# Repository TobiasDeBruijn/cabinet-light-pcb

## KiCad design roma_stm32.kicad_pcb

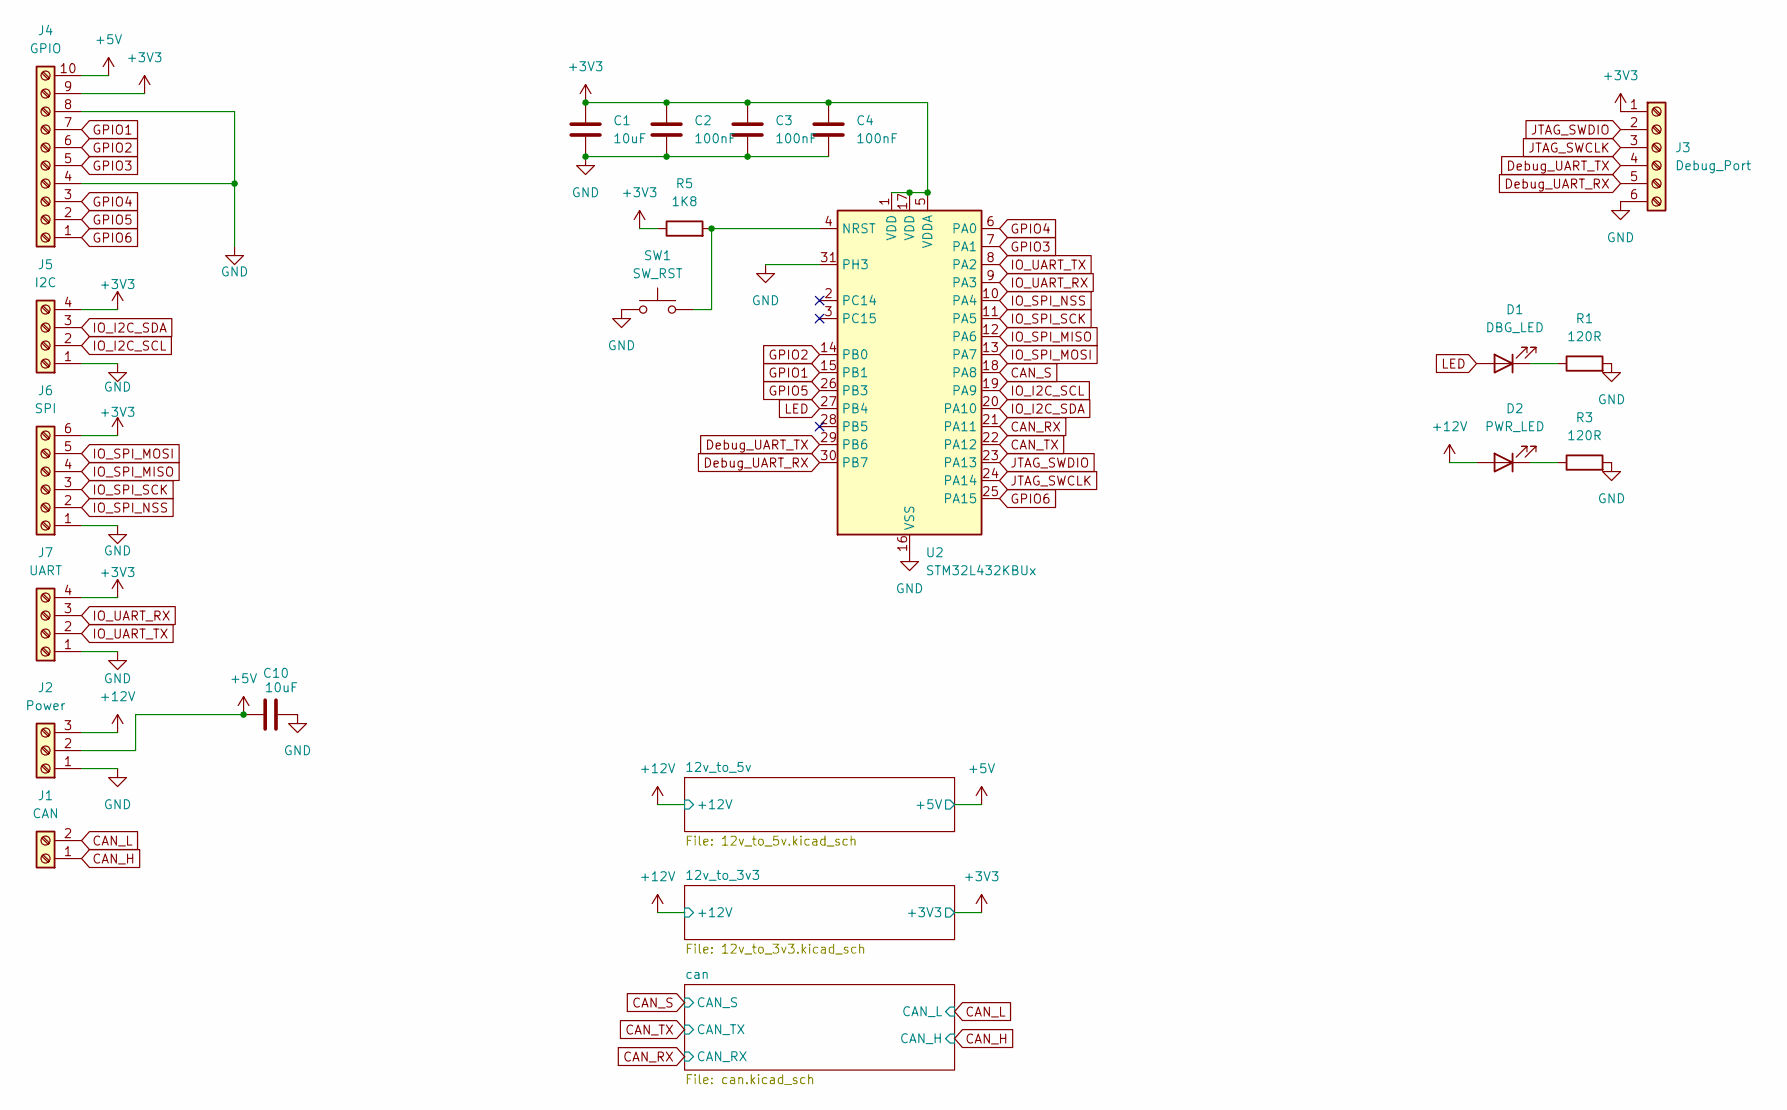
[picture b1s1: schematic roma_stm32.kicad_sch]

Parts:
C1, C10: 10uF; C_0805_2012Metric
C2, C3, C4: 100nF; C_0603_1608Metric
D1: DBG_LED; LED_0805_2012Metric
D2: PWR_LED; LED_0805_2012Metric
J1: CAN; TerminalBlock_Phoenix_PT-1,5-2-5.0-H_1x02_P5.00mm_Horizontal
J2: Power; TerminalBlock_Phoenix_PT-1,5-3-5.0-H_1x03_P5.00mm_Horizontal
J3: Debug_Port; TerminalBlock_Phoenix_PT-1,5-6-5.0-H_1x06_P5.00mm_Horizontal
J4: GPIO; TerminalBlock_Phoenix_PT-1,5-10-5.0-H_1x10_P5.00mm_Horizont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
J5: I2C; TerminalBlock_Phoenix_PT-1,5-4-5.0-H_1x04_P5.00mm_Horizontal
J6: SPI; TerminalBlock_Phoenix_PT-1,5-6-5.0-H_1x06_P5.00mm_Horizontal
J7: UART; TerminalBlock_Phoenix_PT-1,5-4-5.0-H_1x04_P5.00mm_Horizontal
R1, R3: 120R; R_0805_2012Metric
R5: 1K8; R_0603_1608Metric
SW1: SW_RST; SW_Push_1P1T_XKB_TS-1187A
U2: STM32L432KBUx; QFN-32-1EP_5x5mm_P0.5mm_EP3.45x3.45mm

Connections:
+3V3: C1.1, C2.1, C3.1, C4.1, J3.1, J4.9, J5.4, J6.6, J7.4, R5.1, U2.1 (VDD), U2.5 (VDDA), U2.17 (VDD); also elsewhere on the board
+5V: C10.1, J2.2, J4.10; also elsewhere on the board
+12V: D2.2 (A), J2.3; also elsewhere on the board
CAN_H: J1.1; also elsewhere on the board
CAN_L: J1.2; also elsewhere on the board
CAN_RX: U2.21 (PA11); also elsewhere on the board
CAN_S: U2.18 (PA8); also elsewhere on the board
CAN_TX: U2.22 (PA12); also elsewhere on the board
Debug_UART_RX: J3.5, U2.30 (PB7)
Debug_UART_TX: J3.4, U2.29 (PB6)
GND: C1.2, C2.2, C3.2, C4.2, C10.2, J2.1, J3.6, J4.4, J4.8, J5.1, J6.1, J7.1, R1.2, R3.2, SW1.1, U2.16 (VSS), U2.31 (PH3), U2.32 (VSS), U2.33 (VSS); also elsewhere on the board
GPIO1: J4.7, U2.15 (PB1)
GPIO2: J4.6, U2.14 (PB0)
GPIO3: J4.5, U2.7 (PA1)
GPIO4: J4.3, U2.6 (PA0)
GPIO5: J4.2, U2.26 (PB3)
GPIO6: J4.1, U2.25 (PA15)
IO_I2C_SCL: J5.2, U2.19 (PA9)
IO_I2C_SDA: J5.3, U2.20 (PA10)
IO_SPI_MISO: J6.4, U2.12 (PA6)
IO_SPI_MOSI: J6.5, U2.13 (PA7)
IO_SPI_NSS: J6.2, U2.10 (PA4)
IO_SPI_SCK: J6.3, U2.11 (PA5)
IO_UART_RX: J7.3, U2.9 (PA3)
IO_UART_TX: J7.2, U2.8 (PA2)
JTAG_SWCLK: J3.3, U2.24 (PA14)
JTAG_SWDIO: J3.2, U2.23 (PA13)
LED: D1.2 (A), U2.27 (PB4)
unnamed: D1.1 (K), R1.1
unnamed: D2.1 (K), R3.1
unnamed: R5.2, SW1.2, U2.4 (NRST)

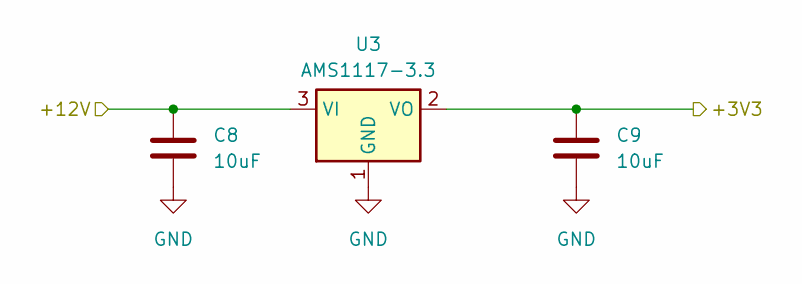
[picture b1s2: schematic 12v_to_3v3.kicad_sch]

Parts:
C8, C9: 10uF; C_0805_2012Metric
U3: AMS1117-3.3; SOT-223-3_TabPin2

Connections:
+3V3: C9.1, U3.2 (VO); also elsewhere on the board
+12V: C8.1, U3.3 (VI); also elsewhere on the board
GND: C8.2, C9.2, U3.1 (GND); also elsewhere on the board

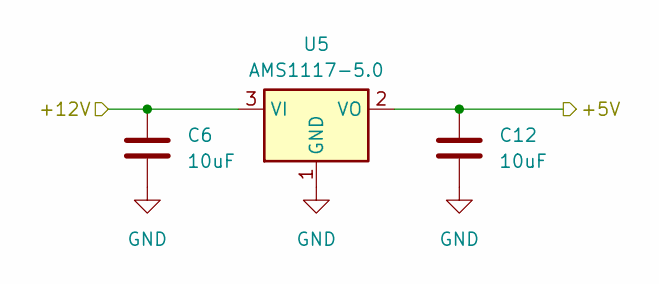
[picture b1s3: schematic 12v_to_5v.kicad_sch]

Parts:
C6, C12: 10uF; C_0805_2012Metric
U5: AMS1117-5.0; SOT-223-3_TabPin2

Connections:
+5V: C12.2, U5.2 (VO); also elsewhere on the board
+12V: C6.2, U5.3 (VI); also elsewhere on the board
GND: C6.1, C12.1, U5.1 (GND); also elsewhere on the board

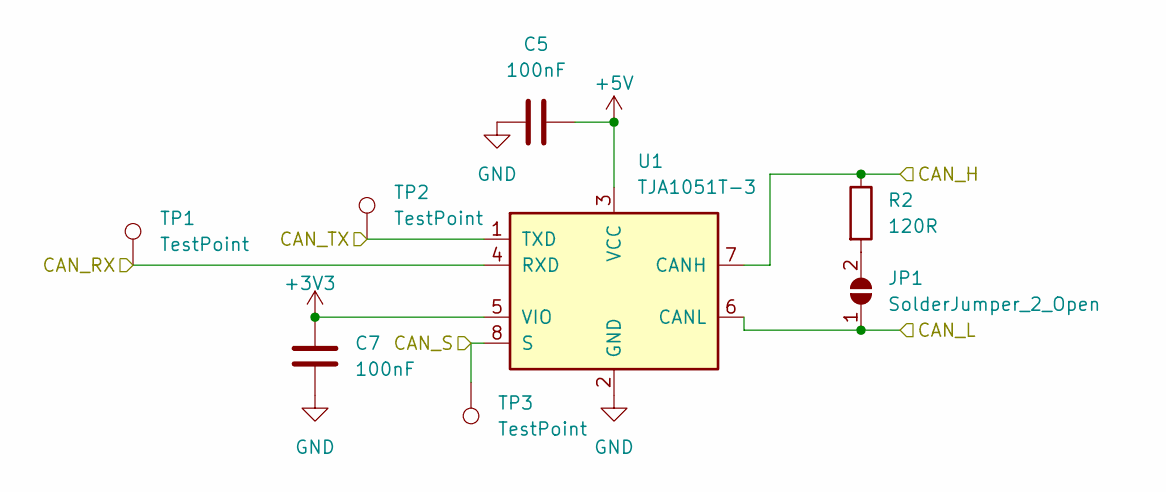
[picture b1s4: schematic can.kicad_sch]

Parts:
C5, C7: 100nF; C_0603_1608Metric
JP1: SolderJumper_2_Open; SolderJumper-2_P1.3mm_Open_Pad1.0x1.5mm
R2: 120R; R_0603_1608Metric
TP1, TP2, TP3: TestPoint; TestPoint_Pad_D1.0mm
U1: TJA1051T-3; SOIC-8_3.9x4.9mm_P1.27mm

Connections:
+3V3: C7.2, U1.5 (VIO); also elsewhere on the board
+5V: C5.2, U1.3 (VCC); also elsewhere on the board
CAN_H: R2.1, U1.7 (CANH); also elsewhere on the board
CAN_L: JP1.1 (A), U1.6 (CANL); also elsewhere on the board
CAN_RX: TP1.1, U1.4 (RXD); also elsewhere on the board
CAN_S: TP3.1, U1.8 (S); also elsewhere on the board
CAN_TX: TP2.1, U1.1 (TXD); also elsewhere on the board
GND: C5.1, C7.1, U1.2 (GND); also elsewhere on the board
unnamed: JP1.2 (B), R2.2

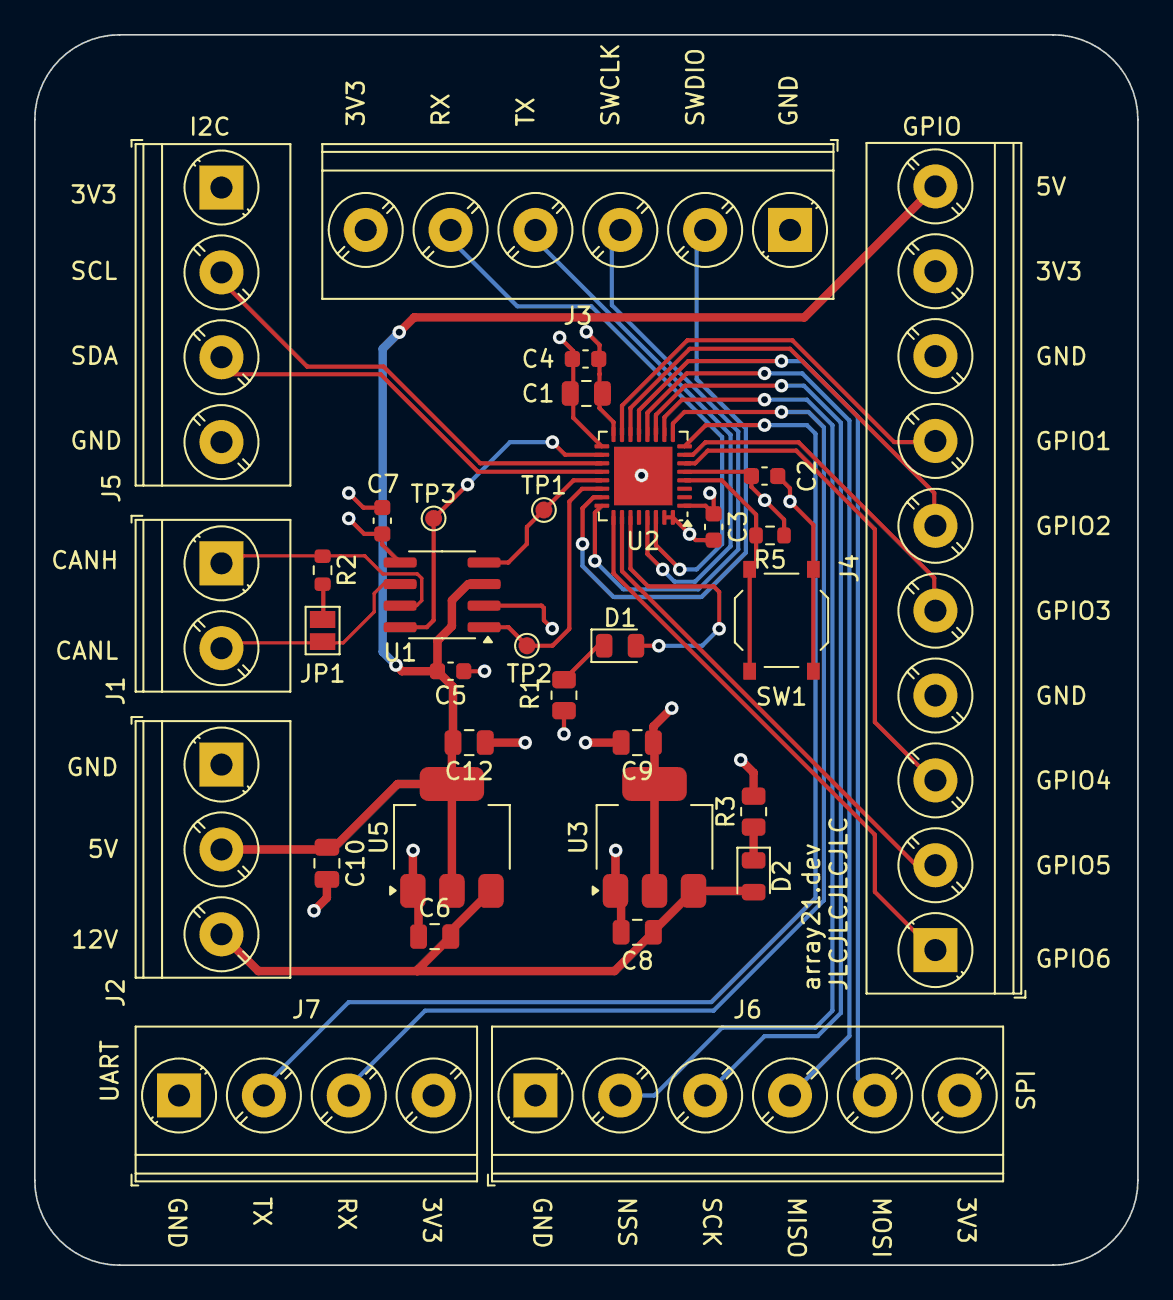
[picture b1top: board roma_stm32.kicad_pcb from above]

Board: 4 copper layers, 65.0 x 72.5 mm, 33 parts (0 on the bottom side), 32 nets.

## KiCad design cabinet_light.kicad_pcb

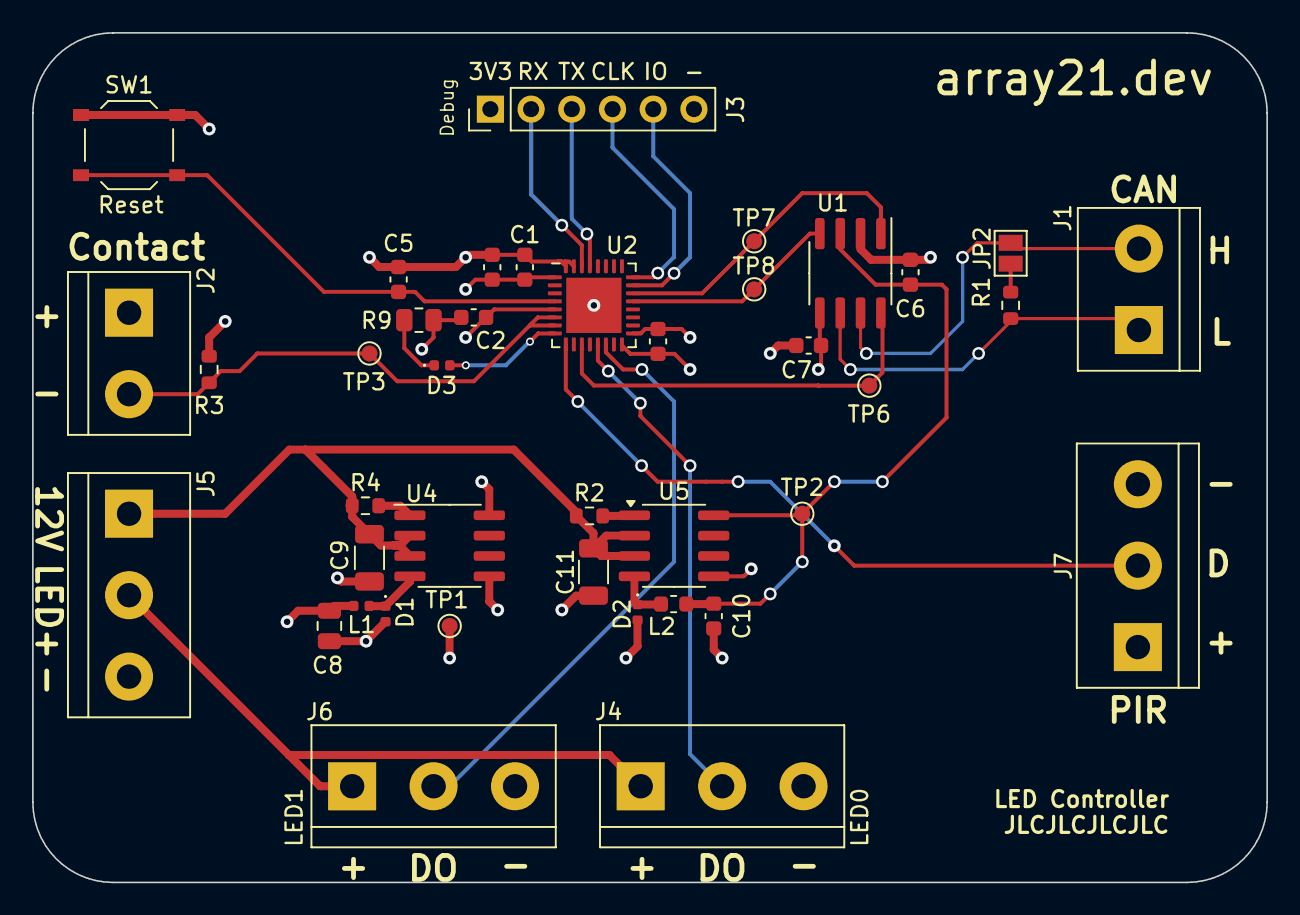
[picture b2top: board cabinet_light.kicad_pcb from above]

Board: 4 copper layers, 77.0 x 53.0 mm, 40 parts (0 on the bottom side), 26 nets.

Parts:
C1, C2, C3, C6, C7: 100nF; C_0603_1608Metric
C4, C5: 10uF; C_0603_1608Metric
C8: 330uF; C_0805_2012Metric
C9, C11: 100uF; C_1206_3216Metric
C10: 330uF; C_0603_1608Metric
D1, D2: D_Schottky; D_0402_1005Metric
D3: LED; LED_0402_1005Metric
J1: CAN; TerminalBlock_bornier-2_P5.08mm
J2: Contact_Sensor; TerminalBlock_bornier-2_P5.08mm
J3: Debug_Port; PinHeader_1x06_P2.54mm_Vertical
J4: LED0; TerminalBlock_bornier-3_P5.08mm
J5: Power_Port; TerminalBlock_bornier-3_P5.08mm
J6: LED1; TerminalBlock_bornier-3_P5.08mm
J7: PIR_Sensor; TerminalBlock_bornier-3_P5.08mm
JP2: CAN_Resistor; SolderJumper-2_P1.3mm_Open_Pad1.0x1.5mm
L1: 1uH; L_0402_1005Metric
L2: 330u; L_0603_1608Metric
R1: 120R; R_0603_1608Metric
R2: 220R; R_0603_1608Metric
R3, R4: 100R; R_0603_1608Metric
R9: 3.3K; R_0805_2012Metric
SW1: SW_RST; SW_Push_1P1T_XKB_TS-1187A
TP1, TP2, TP3, TP6, TP7, TP8: TestPoint; TestPoint_Pad_D1.0mm
U1: TJA1051T-3; SOIC-8_3.9x4.9mm_P1.27mm
U2: STM32L432KBU6; QFN-32-1EP_5x5mm_P0.5mm_EP3.45x3.45mm
U4: ADP1108AR-3.3; SOIC-8_3.9x4.9mm_P1.27mm
U5: ADP1108AR-5; SOIC-8_3.9x4.9mm_P1.27mm

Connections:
+3V3: C1.1, C2.1, C3.1, C4.1, C7.1, C8.1, J2.1, J3.1, J7.1, L1.2, TP1.1, U1.5 (VIO), U2.1 (VDD), U2.5 (VDDA), U2.17 (VDD), U4.8 (SENSE)
+5V: C6.2, C10.1, L2.2, TP2.1, U1.3 (VCC), U5.8 (SENSE)
+12V: C9.1, C11.1, J5.1, R2.1, R4.1, U4.2 (Vin), U4.3 (SW1), U5.2 (Vin), U5.3 (SW1)
CAN+: J1.2, JP2.1 (A), U1.7 (CANH)
CAN-: J1.1, R1.2, U1.6 (CANL)
CAN_RX: TP8.1, U1.4 (RXD), U2.21 (PA11)
CAN_S: TP6.1, U1.8 (S), U2.11 (PA5)
CAN_TX: TP7.1, U1.1 (TXD), U2.22 (PA12)
Debug_UART_RX: J3.2, U2.30 (PB7)
Debug_UART_TX: J3.3, U2.29 (PB6)
Door_Contact: J2.2, R3.1, TP3.1, U2.6 (PA0), U2.7 (PA1)
GND: C1.2, C2.2, C3.2, C4.2, C5.2, C6.1, C7.2, C8.2, C9.2, C10.2, C11.2, D1.2 (A), D2.2 (A), J3.6, J4.3, J5.3, J6.3, J7.3, R3.2, R9.2, SW1.1, U1.2 (GND), U2.16 (VSS), U2.31 (PH3), U2.32 (VSS), U2.33 (VSS), U4.5 (GND), U5.5 (GND)
JTAG_SWCLK: J3.4, U2.24 (PA14)
JTAG_SWDIO: J3.5, U2.23 (PA13)
LED: D3.2 (A), U2.8 (PA2)
LED+: J4.1, J5.2, J6.1
LED_Signal_0: J4.2, U2.13 (PA7)
LED_Signal_1: J6.2, U2.14 (PB0)
unnamed: D1.1 (K), L1.1, U4.4 (SW2)
unnamed: D2.1 (K), L2.1, U5.4 (SW2)
unnamed: D3.1 (K), R9.1
unnamed: JP2.2 (B), R1.1
unnamed: C5.1, SW1.2, U2.4 (NRST)
unnamed: R4.2, U4.1 (Ilim)
unnamed: R2.2, U5.1 (Ilim)
PIR_Signal: J7.2, U2.9 (PA3)

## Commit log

2025-02-26 Woops
2025-02-26 Fix PCB
2025-02-28 WIP: Prepare for JLC
2025-02-28 Replace power regulators; Pick all JLC components
2025-02-28 Attach power LED
